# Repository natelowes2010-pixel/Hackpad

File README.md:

Nate’s Hackpad

A compact 8-key macropad with a rotary encoder, powered by the Xiao RP2040.

CAD Model

PCB

Schematic

Bill of Materials
Qty	Item
1	3D-printed case
8	Mechanical keyboard switches
1	EC11 rotary encoder
1	Xiao RP2040 (DIP)
8	Keycaps
4	M3 × 5 × 4 heat-set inserts
4	M3 × 16 mm socket-head cap screws

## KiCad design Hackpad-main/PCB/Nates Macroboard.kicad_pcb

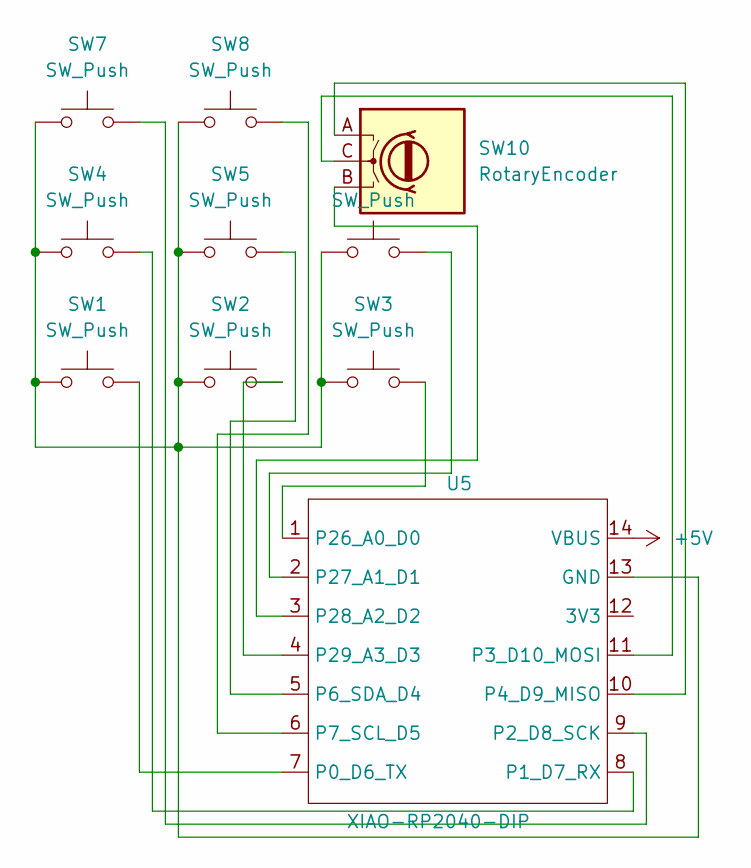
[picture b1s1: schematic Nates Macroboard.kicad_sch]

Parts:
SW1, SW2, SW3, SW4, SW5, SW6, SW7, SW8: SW_Push; SW_Cherry_MX_1.00u_PCB
SW10: RotaryEncoder; RotaryEncoder_Bourns_Vertical_PEC12R-3x17F-Nxxxx
U5: XIAO-RP2040-DIP

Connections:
+5V: U5.14 (VBUS)
unnamed: SW1.1, SW2.1, SW3.1, SW4.1, SW5.1, SW6.1, SW7.1, SW8.1, U5.13 (GND)
unnamed: SW1.2, U5.7 (P0_D6_TX)
unnamed: SW4.2, U5.8 (P1_D7_RX)
unnamed: SW7.2, U5.9 (P2_D8_SCK)
unnamed: SW10.C, U5.11 (P3_D10_MOSI)
unnamed: SW10.A, U5.10 (P4_D9_MISO)
unnamed: SW5.2, U5.5 (P6_SDA_D4)
unnamed: SW8.2, U5.6 (P7_SCL_D5)
unnamed: SW3.2, U5.1 (P26_A0_D0)
unnamed: SW6.2, U5.2 (P27_A1_D1)
unnamed: SW10.B, U5.3 (P28_A2_D2)
unnamed: SW2.2, U5.4 (P29_A3_D3)

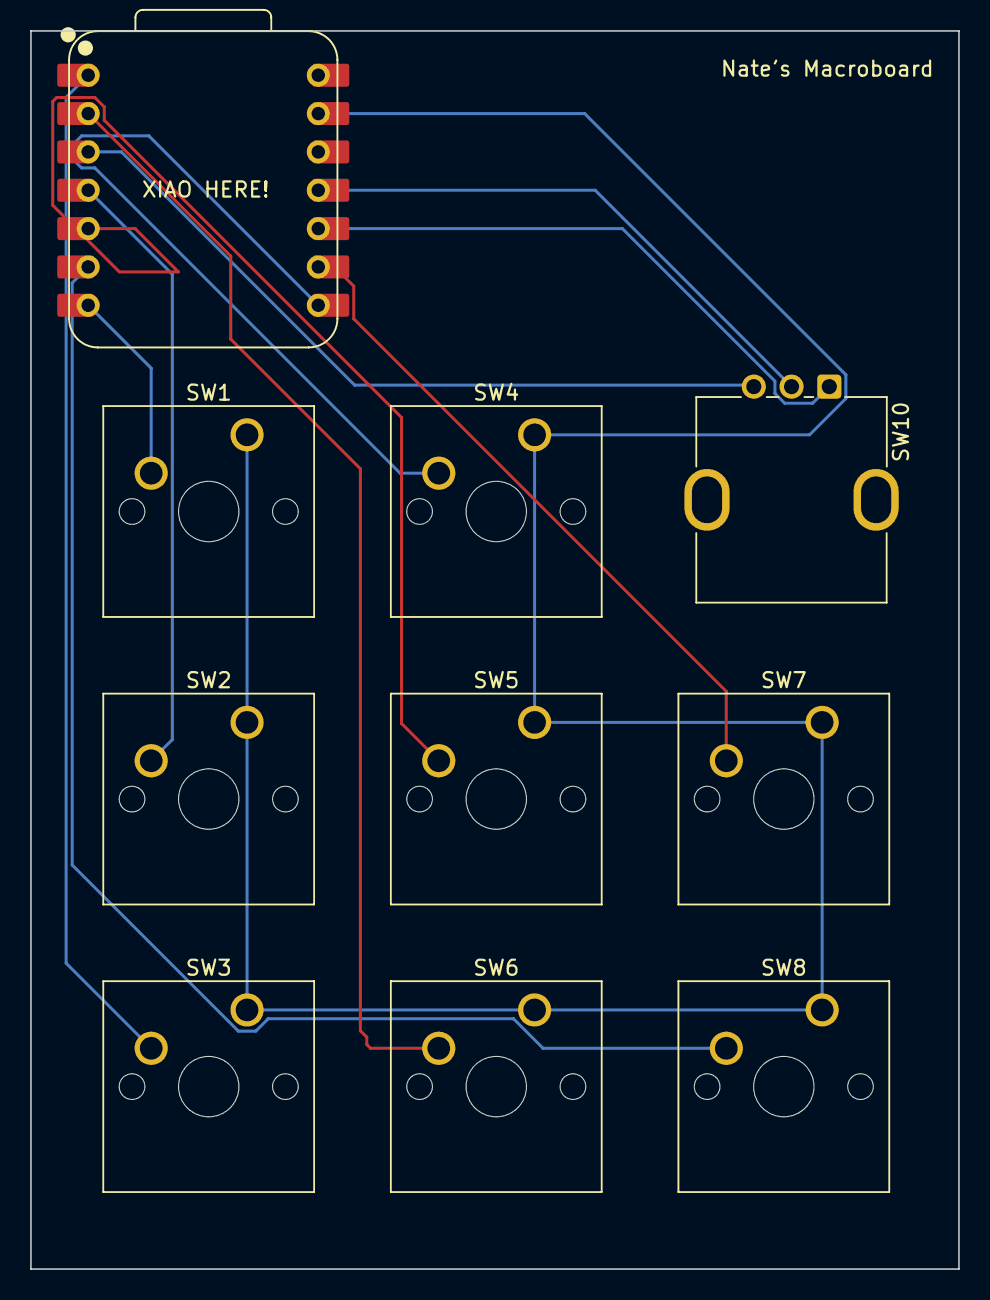
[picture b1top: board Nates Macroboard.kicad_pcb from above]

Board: 2 copper layers, 61.5 x 82.0 mm, 10 parts (0 on the bottom side), 12 nets.
